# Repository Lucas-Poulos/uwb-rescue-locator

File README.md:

# UWB Rescue Locator

Repo: https://github.com/Lucas-Poulos/uwb-rescue-locator

A two-board UWB positioning system for a rescue/safety use case: a
**wristband** worn by a person, and a fixed **bay station** that locates it
in 3D from four anchor points and reports it over Bluetooth LE to a nearby
laptop (with an optional LTE-M uplink from the station).

Positioning is a **hybrid of two-way ranging and TDoA**, not symmetric
multilateration. A center anchor ranges to the tag for distance; three outer
anchors timestamp the same tag transmission and give direction from the
arrival-time differences. The four anchors are **not interchangeable** --
see [`docs/positioning.md`](docs/positioning.md), which is the document to
read first if you're working on anchors, clocking, coax, or connectors.

## Getting started (new contributor setup)

### 1. Install KiCad

The team standard is **KiCad 10.0.5** (see Toolchain below for why).

- **macOS**: `brew install --cask kicad` (Homebrew). If KiCad is already
  installed some other way, add `--force` to overwrite it.
- **Windows/Linux**: download the installer for your platform from
  https://www.kicad.org/download/.

You do **not** need to set any environment variables or configure library
paths yourself -- both boards' `fp-lib-table`/`sym-lib-table` use
`${KIPRJMOD}`-relative paths into this repo's own `shared/` and `libs/`
folders, so cloning the repo anywhere and opening a project just works.

The very first time you launch the KiCad GUI on a given machine, it may
offer to set up its own default global libraries (Device, Connector, etc.)
-- accept the defaults. This is a one-time, per-machine, KiCad-level setup
step, unrelated to this repo.

### 2. Get repo access and clone it

Ask whoever's administering the repo to add you as a collaborator (repo
link at the top of this file), then:

```
git clone git@github.com:Lucas-Poulos/uwb-rescue-locator.git
cd uwb-rescue-locator
```

(Use the HTTPS clone URL instead if you haven't set up an SSH key with
GitHub.)

### 3. Open a board

KiCad doesn't support one project spanning multiple PCBs, so open whichever
board you're working on directly -- there's no single top-level project
file for the whole repo:

```
open wristband/wristband.kicad_pro       # macOS; or just double-click the file
open bay-station/bay-station.kicad_pro
```

### 4. Sanity-check your setup

From a terminal, **outside** this repo (see the `kicad-cli` gotcha further
down for why):

```
cd /tmp
kicad-cli sch erc /path/to/uwb-rescue-locator/wristband/wristband.kicad_sch
```

If this reports a handful of known/expected items (see each board's sheet
table below) rather than a wall of "library not included in configuration"
errors, your KiCad install is set up correctly. If you do see that wall of
errors, see the per-major-version global library table note in Toolchain.

Before pushing anything, also read `CONTRIBUTING.md` -- branch off `main`,
don't edit a sheet someone else is actively working on, and PRs need review
(branch protection is on).

## Status (last updated 2026-11-18)

**Schematic capture is well along on the bay station and early on the
wristband.** On branch `redesign/nrf9151-host` every bay-station sheet has
been wired against one net contract (`docs/net-contract.md`). Neither board
is fab-ready: the bay station still has placeholder footprints on the TCXO,
SMA launch, MAX17048 and DNP eSIM (below). If you're an agent or a new teammate picking this
up cold, read this whole section before touching anything -- it's written to
be a complete handoff.

> ### Architecture change 2026-11-17: nRF9151 host
>
> The bay station's host moved from the Fanstel BT840 (nRF52840) to the
> **Nordic nRF9151** SiP -- LTE-M/NB-IoT modem, built-in GNSS and an
> application core. The nRF91 has no Bluetooth, so the **BT840 stays as a
> UART BLE bridge** to the laptop, and the **MAX-M10S GNSS is gone** (its
> sheet is now `orientation.kicad_sch`). Reasons and the full set of
> consequent calls are in `docs/decisions.md` ("nRF9151 host redesign").
>
> Unchanged, and still the core of the design: four discrete **DW3210**s on
> the one PCB sharing one 38.4 MHz TCXO through a 1:4 buffer, antennas remote
> on coax, A0 doing two-way ranging and A1-A3 TDoA against it
> (`docs/positioning.md`). **Target: 10-30 cm at ~10 m, Channel 5.** No FCC/CE
> work -- university prototype. The critical path is still **array
> calibration**, plus the multi-instance DW3000 driver.

### What exists, per board

The wristband has 7 hierarchical sheets, the bay station 10. Reference designators are
project-wide unique per board (checked 2026-11-17 on the bay station, no
collisions) -- see each `libs/components.csv` for the full part-by-part BOM.

**Wristband** (`wristband/`):
| Sheet | Status | Contents |
|---|---|---|
| Power BMS | **Wired** (global labels, no drawn wires), ERC clean (0 errors) | JST-PH battery -> AO3401A reverse-polarity FET -> TVS -> DW01A+FS8205A protection -> MCP73831 charger (USB-C in) |
| Radio MCU | **Wired**, ERC clean | DWM3001C (U4) + decoupling; SWD, RESET_N, SWO, VBAT_SENSE, SOS button, LED_SYS (P0.14), FW_MARKER (P0.22). One module: DW3110 UWB + nRF52833 MCU + accelerometer + both antennas |
| Mechanical | No wiring needed | 4x M2 mounting holes |
| Regulation | **Wired**, ERC clean | TPS7A0233PDBVR LDO (U5, 3.3V) -- battery hits 4.2V, DWM3001C tops out at 3.6V |
| Programming/Debug | **Wired**, ERC clean | ARM Cortex Debug SWD header (J3), targeting the nRF52833 inside U4 |
| Indicators | **Wired**, ERC clean | System LED D4 + R13 on nRF52833 P0.14; the charge LED (D2/R10, MCP73831 STAT) lives on Power BMS |
| Test Points | **Wired**, ERC clean | TP1-TP5: +3V3, VBAT, 2x GND, FW_MARKER (P0.22) |

**Bay Station** (`bay-station/`) -- per-sheet detail in each
`bay-station/*_notes.md`; sheet-by-sheet summary in `bay-station/README.md`:
| Sheet | Status | Contents |
|---|---|---|
| Power BMS | **Wired** | Barrel jack + USB-C -> MCP73871 power-path charger -> MAX17048 fuel gauge; backup cell with AO3401A + TVS. THERM window sized for cold-charge cutoff |
| Regulation | **Wired** | U8 TPS62A02 -> `+3V3`; **U40 TPS63802 buck-boost -> `+VBAT_LTE`** (nRF9151 VDD, 3.59 V); `+3V3` sequenced >= 6 ms after it; PPK2 break links on both rails |
| Connectivity | **Wired** | **nRF9151 (U20)** host with Nordic's HDG decoupling, LTE + GNSS (BGA524N6 LNA) on u.FL, nano-SIM (+ DNP eSIM); **BT840 (U3)** as UART BLE bridge |
| UWB Array | **Wired** | 4x DW3210 (U4=A0 center, U5-U7=A1-A3 outer), Qorvo Fig 32 decoupling, per-anchor 0R rework links, pi-match pads, SMA J20-J23 (proposed CONSMA020.042-G) |
| Clock Distribution | **Wired** | Proposed Rakon RPT1490LN TCXO -> TI LMK1C1104 1:4 buffer -> 2200 pF -> each XTI |
| Orientation (was GNSS / Orientation) | **Wired** | IIS2MDC magnetometer (U10, 0x1E) + IIS2DLPC accelerometer (U11, 0x19) |
| Indicators | **Wired** | D4-D6 charger status, D7 `LED_SYS`, D400 `LED_LTE`, D401 `LED_LINK`, resistors computed per rail |
| Programming/Debug | **Wired** | J3 nRF9151 SWD, J32 BT840 SWD, DNP Tag-Connect pads, J33 debug UART, SW2/SW11 resets, SW12 user button |
| Test Points | **Wired** | 64 pads covering every net-contract net (+ local pads on each sheet); index in `docs/verification-plan.md` |
| Mechanical | Placement only | 4x M3 mounting holes, 3 fiducials |

Whole-project ERC after the merge (2026-11-17, `kicad-cli` 10.0.5,
`--severity-all`): **7 warnings, 0 errors**, down from 596, with 432
components loaded (so not the silent `extends` failure). All 7 are
library-copy warnings, none connectivity: six `lib_symbol_mismatch` on
flattened stock symbols (BT1, Q1, J2, TH1, J3, J32) and, since the U8 lib_id
was renamed to `TPS62A02PDDC` on 2026-11-18, U8 (same count: the former
`lib_symbol_issues` became a seventh `lib_symbol_mismatch`; see
`docs/decisions.md`). The 97 `unconnected-*` nets
in the netlist are deliberate no-connect flags (spare BT840 GPIOs, nRF9151
reserved/MAGPIO pins, unused header pins). Per-sheet before/after counts are
in `bay-station/handoff/`.

### Confirmed chips/ICs (all sourced against real datasheets, not guessed)

| Part number | Role | Board(s) | Qty |
|---|---|---|---|
| Qorvo **DWM3001C** | UWB transceiver + nRF52833 MCU + LIS2DH12 accelerometer + both antennas, one module. Replaced NINA-B111 + DWM3000 + the antenna sheet | Wristband | 1 |
| Qorvo **DW3210** | Discrete UWB transceiver IC, QFN-40 5x5mm. One per anchor (U4=A0 center, U5-U7=A1-A3 outer). Chosen over the DWM3000 module because the module exposes no clock pin, and a shared reference is what makes the TDoA array work -- see `docs/positioning.md` | Bay Station | 4 |
| Qorvo **DWM3000** | UWB transceiver module. **No longer used on either board** -- the wristband moved to the DWM3001C and the bay station to discrete DW3210. Symbol and footprint are retained in `shared/` for reference only | -- | 0 |
| Microchip **MCP73831** | LiPo linear battery charger | Wristband | 1 |
| Fortune Semiconductor **DW01A** | Battery protection IC | Wristband | 1 |
| Fortune Semiconductor **FS8205** (commonly sold as "FS8205A" -- see `wristband/libs/README.md`) | Protection dual MOSFET, DW01A's partner IC | Wristband | 1 |
| AOS **AO3401A** | Reverse-battery-polarity protection P-MOSFET ("ideal diode") | Wristband + Bay Station | 2 |
| onsemi **ESD5B5.0ST1G** | TVS diode, battery/power-input protection | Wristband (1) + Bay Station (2) | 3 |
| Nordic **nRF9151** (nRF9151-LACA-R7) | Host SiP: LTE-M/NB-IoT modem + GNSS + Cortex-M33. Replaced the BT840 as host 2026-11-17. Footprint from Nordic's DK files (2026-11-18) | Bay Station | 1 |
| Fanstel **BT840** (Nordic nRF52840) | UART BLE bridge to the laptop (host until 2026-11-17; replaced ESP32-S3-WROOM-1 before that) | Bay Station | 1 |
| Microchip **MCP73871** | Charge management + power-path IC | Bay Station | 1 |
| Maxim/Analog Devices **MAX17048** | Battery fuel gauge (SOC monitor) | Bay Station | 1 |
| TI **TPS7A0233PDBVR** | LDO regulator (3.3V) -- battery rail can hit 4.2V, which exceeds the DWM3001C's 3.6V operating max without this. Replaced the MCP1700 on 2026-09-23 | Wristband | 1 |
| TI **TPS62A02PDDCR** | Buck regulator, `+VSYS` -> `+3V3` | Bay Station | 1 |
| TI **TPS63802DLAR** | Buck-boost, `+VSYS` -> `+VBAT_LTE` (nRF9151 VDD). Footprint from TI's land-pattern page (2026-11-18) | Bay Station | 1 |
| ST **IIS2MDC** / **IIS2DLPC** | Magnetometer (heading) / accelerometer (tilt, knock). Industrial grade with ST's 10-year longevity commitment; replaced the terminated LIS3MDL and the obsolete LIS2DH on 2026-11-18 | Bay Station | 1 + 1 |
| Infineon **BGA524N6** + TI **TPS7A0228** | GNSS LNA and its COEX0-switched 2.8 V LDO, as on the nRF9151 DK | Bay Station | 1 + 1 |
| TI **TPD3F303** | SIM ESD/EMI filter | Bay Station | 1 |
| Rakon **RPT1490LN** / TI **LMK1C1104** | 38.4 MHz CMOS TCXO / 1:4 clock buffer -- **PROPOSED**; the TCXO looks quote-only | Bay Station | 1 + 1 |

Footprint caveats: MAX17048 is flagged `_PLACEHOLDER` in its footprint file
-- pin/electrical data is fully verified, but one land-pattern dimension
needs re-checking against the real datasheet figure before fab (see
`bay-station/libs/README.md`). The same caveat applies to the DWM3000
footprint retained in `shared/`, though nothing uses it now. On the bay
station, the nRF9151 (U20), BT840 (U3) and TPS63802 (U40) footprints were
replaced on 2026-11-18 with vendor-sourced geometry (`docs/decisions.md`,
Resolved); the Rakon TCXO, the SMA edge launch (needs EM simulation) and the
DNP eSIM are still placeholders.

`U3` on both boards (BT840 and DWM3001C) and bay-station FB1-FB4 were given
footprints on 2026-11-18 (BT840 from Fanstel's library, DWM3001C from Qorvo's;
FB1-FB4 use stock 0201 pads, Murata land table not yet read).

Standard passive size for this whole project: **0603** for R/C/L (0-ohm
0603 link/jumper resistors are documented as a standard available option in
each `components.csv`, not yet placed on any sheet -- no specific
strap/bridge need identified yet).

Full reasoning/history for every choice above, plus the still-open
decisions (anchor placement, uplink backend, etc.), is in
`docs/decisions.md`.

### Known gotchas for whoever (human or agent) works on this next

- **kicad-cli silently fails on `extends`-based symbols.** Any cached
  schematic symbol using KiCad's `extends` mechanism (e.g. the default
  `AO3401A extends TP0610T`) makes `kicad-cli` fail to load the *entire
  file* and silently report it as empty (0 components, 0 ERC violations)
  rather than erroring loudly. Both boards work around this by embedding a
  flattened, non-`extends` copy of AO3401A. If a future sheet adds another
  `extends`-based part and ERC suspiciously shows 0 violations, check this
  first.
- **Always run `kicad-cli` from a scratch directory, never from inside a
  git repo.** It writes `.rpt` report files to the current working
  directory as a side effect; running it from inside a repo pollutes that
  repo's working tree with stray files.
- **KiCad's global library table is per-major-version and doesn't
  auto-populate from `kicad-cli` alone** -- see the Toolchain section below.
- **Don't leave a KiCad GUI window open on a project while also editing its
  files by hand/via script.** This happened once already: a background GUI
  session silently resaved `bay-station/power_bms.kicad_sch` in KiCad 10
  format while a concurrent edit was adding new sheets to the root file. No
  data was lost (verified via a reference-designator diff before
  committing), but it could have silently clobbered the newer edits if the
  stale window had been saved again afterward. Close/reload any open KiCad
  windows before doing further programmatic edits, and vice versa.
- The sibling project at `~/kicad-projects/wristband-alarm` (a *different*,
  unrelated wristband-alarm concept, also u-blox NINA-based) has its own
  long-standing uncommitted working-tree state -- don't touch it, don't
  assume its README reflects its actual working tree.

### Branches and workflow (as of 2026-11-18)

**There is no PR workflow.** Commit straight to the trunk branch and push;
no review gate (`CONTRIBUTING.md`, root `CLAUDE.md` rule 5). The trunk is
**`redesign/nrf9151-host`** -- the nRF9151-host bay station, the DW3210 array
and everything in this README -- until it replaces `main`. `main` still holds
the pre-redesign state (BT840 host, MAX-M10S) and is not where work happens;
branch protection on it has to be relaxed before anything can be pushed there.

What is where, so nobody resurrects the wrong thing:

- **Already merged into `main`** (before the redesign, all contained in the
  trunk): the Design Specifications section, the bay station power/regulation/
  programming-debug wiring pass, the no-external-wristband-IMU decision, PR #9
  (I2C pull-ups R37-R39) and PR #8 (per-anchor DW3210 decoupling, C40-C74 +
  FB1-FB4 + R33-R36, from Qorvo's reference design).
- **Superseded, do not merge: PR #7 / `feat/bay-station-wifi`** (ESP32-C5
  Wi-Fi co-processor). The nRF9151 redesign replaced the host it was written
  against; the station's second uplink is LTE-M, and there are no GPIOs left
  for a Wi-Fi co-processor (`docs/decisions.md`, Resolved, "Process"). The
  GitHub PR is still open and can be closed from the web UI.
- **Historical branches, not ancestors of the trunk:** `dwm3001c-migration`
  (the wristband work; it landed on `main` through the rebased branch in
  PR #5, so the original is redundant), `backup/dwm3001c-pre-rebase` (a
  safety copy of the same), and `nina-b400-migration` (an earlier u-blox
  NINA-B400 / DWM3000-module schematic pass, last touched 2026-09-20; its
  contents were not reviewed for this rewrite). Reference only -- run
  `git branch -a --no-merged redesign/nrf9151-host` before assuming a branch
  holds work that matters.

Merging history worth knowing: PR #8 and PR #9 conflicted textually with the
power-wiring pass because `connectivity.kicad_sch` and `uwb_array.kicad_sch`
had been reserialized to KiCad 10 format in between, and were hand-ported onto
the reserialized files (`b7ab51f`, `4ef1099`; balanced parens, no duplicate
references, ERC showing exactly the expected violation delta). That was done
carefully and checked, not the norm -- `CONTRIBUTING.md`'s warning about
silent corruption from hand-resolving `.kicad_sch` conflicts still stands.

### Not done yet (in rough next-up order)

1. **Re-verify every Nordic fact against the PDFs** -- so far they were
   read only from Nordic's HTML pages (`docs/decisions.md`, Open). The
   nRF9151 footprint itself now comes from Nordic's DK files; compare it with
   the PS land-pattern figure when the PDF is in hand.
2. **Footprints**: BT840, DWM3001C, U40 and nRF9151 are done (2026-11-18);
   still open are FB1-FB4 (read Murata's BLM03PG land table), the TCXO,
   the SMA launch and the DNP eSIM.
3. **Close the redesign's open risks** in `docs/decisions.md`. Analysed
   2026-11-18 and reduced to concrete actions: the DW3210 has **no exposed
   pad** (footprint since replaced), the 8 MHz SPI cap is a reply-delay
   measurement not a throughput problem, XTI amplitude is at the DW3000 limit
   and needs a bench check, and there is a ranked list of ways to free GPIOs
   (one is free since the sensor re-pick: P0.24). The terminated LIS3MDL and
   obsolete LIS2DH were replaced by the IIS2MDC / IIS2DLPC on 2026-11-18. Still open: TCXO availability (quote), GNSS LNA
   pre-filter.
4. **Array calibration procedure and fixture** -- the project's critical
   path; drafted in `docs/verification-plan.md`.
5. **Firmware**: the NCS skeletons exist but have never been built; the
   multi-instance DW3000 driver is the gating task (`firmware/README.md`).
6. Wire the wristband's placement-only sheets (independent of everything
   above).
7. PCB layout. The bay station's `.kicad_pcb` has its **4-layer
   controlled-impedance stackup** set from DW3000 Section 7.3.2 Figure 35
   (1.048mm finished); since 2026-11-18 it also has the board outline and all 428 footprints placed (unrouted;
   `docs/layout-notes.md`).
   **The wristband's `.kicad_pcb` is not an empty stub** -- it already carries
   36 footprints, a routed board outline, and real DRC findings from the
   DWM3001C migration (PR #5); U3 (the DWM3001C) now has a footprint in the library (2026-11-18) but the PCB
   still embeds the old placeholder until it is updated from the schematic.

Done since the last update, for the record: the anchor rework onto four
discrete DW3210s, the decoupling audit (`docs/passives-reference.md`), the
two-USB-C item (deleted with the ESP32), the antenna-matching task (deleted
with the wristband's antenna sheet), the L1 and SW2 footprints, the
cold-charge THERM sizing, and the bay station's GPIO allocation.

## System overview

```
                         A1 ← antenna on coax
                            \
   ┌─────────────┐           \      ┌────────────────────────────┐
   │  Wristband   │  UWB       ○────│  Bay Station (ONE PCB)     │
   │  (worn tag)  │ ═════════▶ A0   │  4x DW3210, one TCXO       │
   └─────────────┘  one TX    / \   │  nRF9151 host (LTE-M+GNSS) │
                             /   \  │  BT840 BLE bridge (UART)   │
                           A2     A3└──────┬──────────────┬──────┘
                      antennas on ~1-2 m   │ Bluetooth LE │ LTE-M
                      coax, rigid frame    ▼              ▼ (optional)
                                         Laptop        network

   A0     two-way ranging  -> range to tag
   A1-A3  TDoA vs. A0      -> direction to tag

   All four transceivers share one clock on the board.
   Only the antennas are remote.
```

- **Wristband**: one Qorvo DWM3001C (UWB + nRF52833 MCU + antennas) +
  a compact BMS (MCP73831 charger + DW01A/FS8205 protection + AO3401A
  reverse-polarity protection). Design compromises favor small size and
  just enough battery life to get core functionality working. In the
  positioning scheme its job is simply to transmit -- one transmission
  yields all four measurements, deliberately, because the tag is the
  power-constrained side.
- **Bay station**: four UWB receivers in two roles (one center, three outer)
  on a single PCB sharing one TCXO, an nRF9151 host (LTE-M + GNSS) with a
  Fanstel BT840 bridging to a laptop over BLE, and a BMS designed for long
  runtime rather than small size (MCP73871 power-path charger + MAX17048 fuel
  gauge), since the bay station isn't worn. The four antennas sit on ~1-2 m coax runs to a rigid frame --
  that's what buys the baseline the bearing measurement needs.

There's no physical connector between the wristband and the bay station --
their only interface is the UWB radio link. The bay station's own antennas
are wired to it over SMA coax (CH5 at 6489.6 MHz is above U.FL's 6 GHz
rating). See `docs/system-overview.md` and `docs/positioning.md`.

## Design specifications

Quick-reference only -- full reasoning, error budgets, and datasheet
citations live in `docs/positioning.md` (RF/clock/mechanical) and
`docs/decisions.md` (every component/architecture call). Anything not listed
here as resolved is still an open decision; check there before assuming a
number is final.

**Performance target**
| | |
|---|---|
| Accuracy | 10-30 cm |
| Range | ~10 m |
| Baseline (A0-to-outer-antenna spacing) | ~1 m as built; frame size is the real limit, not cable loss |

**RF**
| | |
|---|---|
| UWB channel | Channel 5, 6489.6 MHz |
| UWB IC, bay station | 4x Qorvo DW3210 (QFN40, non-PDoA) -- U4=A0 center, U5-U7=A1-A3 outer |
| UWB IC, wristband | Qorvo DW3110 (WLCSP), inside the DWM3001C module |
| UWB connectors | SMA -- CH5 is above U.FL/W.FL/MMCX/MCX's 6 GHz rating and SMB's 4 GHz rating |
| Link budget | 86 dB available (CH5, 850 kbps, 1024-symbol preamble); ~17 dB margin at 10 m |
| Antennas (bay station) | Not yet selected -- candidates covering CH5: Taoglas UWC.01 / ILA.68 / UWCCP.01 |

**Clock (bay station array)**
| | |
|---|---|
| Reference | One 38.4 MHz TCXO -> 1:4 low-skew fan-out buffer -> all 4 DW3210 XTI pins |
| Coupling | 2200 pF AC-coupled into each XTI; 1 pF from each XTO to ground |
| TCXO spec | 0.8 V-VDD2 Vpp, -132 dBc/Hz @ 1 kHz, -145 dBc/Hz @ 10 kHz, 40-60% duty (DW3000 Datasheet Table 10) |
| TCXO + buffer part numbers | Rakon RPT1490LN + TI LMK1C1104 -- PROPOSED, TCXO availability open |

**Positioning architecture**
Hybrid two-way-ranging + TDoA, not symmetric multilateration -- see
`docs/positioning.md` for the full derivation.
| | |
|---|---|
| Center anchor (A0) | Two-way ranging with the wristband -> range |
| Outer anchors (A1-A3) | TDoA vs. A0 on the same tag transmission -> direction |
| System | 4 equations, 3 unknowns -- overdetermined by 1; use the residual as a quality metric |
| Mechanical | Rigid frame fixes geometry (no install-time survey); A0 offset 20-30 cm out of the A1-A3 plane to avoid a mirror ambiguity |
| Array calibration | Required, not optional (generic +/-6 cm spec is 3x too loose at this baseline); procedure/fixture still open |

**Power**
| | Wristband | Bay station |
|---|---|---|
| Regulator | TI TPS7A0233PDBVR LDO, 3.3V | TI TPS62A02PDDCR buck -> `+3V3`, 2A; TI TPS63802 buck-boost -> `+VBAT_LTE` 3.59 V, 2A |
| Load vs. rating | ~43 mA (4.6x headroom) | `+3V3` ~356 mA peak (~446 mA worst case); `+VBAT_LTE` 505 mA LTE TX subframe -- >= 4x headroom on both (`docs/decisions.md`) |
| Standby | ~2.7 uA | n/a -- BMS optimized for runtime, not size |

**Connectivity**
| | |
|---|---|
| Wristband <-> bay station | UWB only -- one tag transmission per exchange, no other radio link |
| Bay station -> laptop | Bluetooth LE via the BT840 bridge (NUS, framed relay, raw timestamps) -- primary path, no WiFi |
| Bay station -> network | LTE-M from the nRF9151, optional (station must work with no SIM); service still open |
| Georeferencing | nRF9151 GNSS (time-shared with LTE) + ST IIS2MDC magnetometer + ST IIS2DLPC accelerometer (bay station only; position + heading both required) |

**Cost** (one prototype pair, hobbyist qty-1 pricing -- see `docs/bom-cost.md`)
| | |
|---|---|
| Wristband | ~$67 |
| Bay station | ~$263 + unpriced rows (nRF9151, TCXO, ...) |
| Total | ~$330 + unpriced rows |

**Regulatory**
No FCC/CE certification -- university prototype, not sold or deployed as a
product. Revisit as a first-class schedule item if that ever changes.

**Toolchain**
| | |
|---|---|
| KiCad | 10.0.5 (files on disk still in 8.0 format) |
| MCUs | All Nordic -- nRF52833 (wristband, inside DWM3001C) / nRF9151 host + nRF52840 BLE bridge (bay station, the latter inside the Fanstel BT840) |
| Firmware SDK | nRF Connect SDK v3.4.x (LTS), all images; nRF9151 modem FW 2.0.4 |

## Repo layout

```
shared/                      # symbols/footprints/3D models used on BOTH boards (e.g. the UWB IC)
  symbols/                   # shared .kicad_sym library
  footprints/                # shared .pretty footprint library
  3dmodels/                  # shared .step/.wrl models
wristband/                   # KiCad project: the wearable tag
  wristband.kicad_pro/sch/pcb
  libs/                      # wristband-only symbols/footprints
bay-station/                 # KiCad project: the fixed 4-anchor station
  bay-station.kicad_pro/sch/pcb
  libs/                      # bay-station-only symbols/footprints
docs/
  positioning.md             # the ToF + TDoA scheme, error budget, clock architecture
  system-overview.md         # block diagram + RF/data interface between the boards
  decisions.md               # open + resolved component/architecture decisions log
  passives-reference.md      # every chip's reference-design passives, compiled per-chip
  bom-cost.md                # build cost estimate for one prototype pair
  net-contract.md            # bay-station cross-sheet net names
  verification-plan.md       # bay-station bring-up/test plan + test-point index
firmware/                    # NCS firmware (nRF9151 / BT840 / nRF52833) -- skeletons, never built
CLAUDE.md                    # working rules for Claude Code / other coding agents
CONTRIBUTING.md              # git workflow, sheet conventions, pre-push checks
```

Each board is its own KiCad project (KiCad doesn't support one project
spanning multiple PCBs), but both live in this one repo so shared parts,
docs, and history stay in one place. Each project's `fp-lib-table` /
`sym-lib-table` reference the `shared/` libraries via `${KIPRJMOD}` relative
paths, so this works regardless of where the repo is cloned -- no per-machine
setup needed.

## Toolchain

Files are currently in **KiCad 8.0** format, originally authored/verified
against KiCad 8.0.6. As of 2026-08-14 this machine has been upgraded to
**KiCad 10.0.5** (the actual current stable -- confirmed as the team's
standard, superseding an earlier, since-corrected plan to target KiCad 9.x).
All existing files were re-checked with
`kicad-cli` under 10.0.5 (`sch erc`/`pcb drc`) and open/parse cleanly with no
new issues -- opening a file in the newer GUI and re-saving is still a
one-way, zero-cost upgrade whenever the team wants to bump the file format
itself; nothing has been re-saved yet, so the files on disk are still 8.0
format.

Note for anyone else upgrading KiCad's major version: `kicad-cli` alone
won't auto-populate the new version's global symbol/footprint library table
(`~/Library/Preferences/kicad/<version>/sym-lib-table` /`fp-lib-table`) --
that normally happens the first time you launch the actual KiCad GUI and it
offers to migrate/create settings. If you only ever use `kicad-cli`
headlessly without opening the GUI first, you may see a wall of spurious
"library not included in configuration" ERC errors -- just launch KiCad.app
once (or copy the two `*-lib-table` files from
`.../KiCad.app/Contents/SharedSupport/template/`) to fix it.

## Using Claude Code (or another coding agent) on this project

**The working rules for agents live in [`CLAUDE.md`](CLAUDE.md)** -- Claude
Code picks that up automatically. This section is the human-readable version
of why those rules exist.

KiCad's file formats (`.kicad_sch`, `.kicad_pcb`, `.kicad_pro`, `.kicad_sym`,
`.kicad_mod`) are plain text (S-expression or JSON) -- an agent can read and
edit them directly like any other source file, no special MCP server or
plugin required. Everything in this repo so far was built that way. A few
things make it work reliably, several of them learned the hard way in this
repo's own history:

- **`kicad-cli` is the fast headless sanity check.** After any edit, run
  `kicad-cli sch erc <board>.kicad_sch` and `kicad-cli pcb drc
  <board>.kicad_pcb` before trusting a change.
  - **macOS**: a Homebrew install symlinks it onto `PATH` automatically
    (`/opt/homebrew/bin/kicad-cli`); otherwise it's inside the app bundle at
    `/Applications/KiCad/KiCad.app/Contents/MacOS/kicad-cli`.
  - **Windows**: the official installer puts it on `PATH` automatically; if
    not, it's at `C:\Program Files\KiCad\10.0\bin\kicad-cli.exe`.
  - **Linux**: on `PATH` automatically via most package managers (apt,
    dnf, etc.) or the official AppImage/flatpak.
- **Always run `kicad-cli` from a scratch/temp directory, never from
  inside this repo.** It writes `.rpt` report files to the current working
  directory as a side effect -- running it from inside a git repo (this
  one or any other) pollutes the working tree with stray files. This has
  actually happened once already, to an unrelated sibling project, from a
  leftover `cd`.
- **`kicad-cli` silently fails on `extends`-based symbols.** A cached
  schematic symbol using KiCad's `extends` mechanism (e.g. the default
  library's `AO3401A extends TP0610T`) makes `kicad-cli` fail to load the
  *entire file* and report it as empty (0 components, 0 ERC violations)
  instead of erroring loudly -- a suspiciously clean ERC run is a red flag,
  not necessarily good news. This repo works around it everywhere by
  embedding flattened, non-`extends` copies of any such symbols (see
  `docs/decisions.md` and the various `*_notes.md` files for examples).
- **Use an existing sheet/symbol/footprint as the format template before
  writing a new one.** Every file in this repo was built by reading a
  known-good file first -- either one already in this repo, or one of
  KiCad's own bundled default libraries -- and matching its exact
  structure, rather than freehand-authoring the s-expression format from
  memory. This repo uses literal tab characters for indentation, not
  spaces; match that.
- **Don't run scripted file edits at the same time as a live KiCad GUI
  session has the same project open.** A background GUI window doesn't
  know about changes made outside it, and saving from a stale window can
  silently overwrite newer edits -- this already caused one near-miss on
  the bay station board (see "Known gotchas" above). Close/reload any open
  KiCad windows before scripted edits, and vice versa. A lock file at
  `<board>/~<board>.kicad_pro.lck` means a GUI session currently has that
  project open.
- **Verify real datasheet facts (pinouts, voltage ratings, current draw)
  by actually fetching and reading the datasheet PDF**, not from memory or
  a search-result summary -- several real bugs/gaps in this repo were only
  caught this way (e.g. the wristband's missing voltage regulator, a
  part-number that doesn't actually exist, a mislabeled SOT-23-6 part).
- **pcbnew's Python bindings** are available for programmatic
  footprint/board work (generating a blank `.kicad_pcb`, loading a
  footprint to sanity-check its pad count, etc.) via KiCad's own bundled
  Python interpreter -- **not** your system Python, which won't have the
  `pcbnew` module installed:
  - **macOS**: `/Applications/KiCad/KiCad.app/Contents/Frameworks/Python.framework/Versions/Current/bin/python3`
  - **Windows**: typically `C:\Program Files\KiCad\10.0\bin\python.exe`
  - **Linux**: usually just your system `python3` if KiCad was installed via
    a package manager that wires up the `pcbnew` module for it; otherwise
    check your distro's KiCad packaging docs.

## Will this work on both Mac and Windows?

Yes, and this has actually been checked, not just assumed:

- No absolute Mac-specific paths are baked into any `.kicad_pro`/`.kicad_sch`/
  `.kicad_pcb`/library file (`git grep`-checked) -- all cross-file/library
  references use `${KIPRJMOD}`-relative paths, which KiCad resolves
  identically on every OS.
- No filenames in this repo use characters or reserved names that are
  illegal on Windows (`: * ? " < > |`, or `CON`/`PRN`/`AUX`/`NUL`/`COM1-9`/
  `LPT1-9`), and no path exceeds even a fraction of Windows' historical
  260-character path limit (longest path in this repo is 80 characters).
- All tracked files use consistent LF line endings, and `.gitattributes`
  normalizes this going forward so a Windows contributor's git config
  (which sometimes auto-converts line endings on checkout) can't silently
  turn KiCad files into CRLF and create noisy diffs or merge pain.

What differs by platform is purely the install step and a couple of tool
paths (both covered above/in Getting Started) -- KiCad itself, the file
formats, and this repo's structure are fully cross-platform.

## Contributing

See `CONTRIBUTING.md` for the git workflow (branching, hierarchical-sheet
conventions to avoid merge conflicts, pre-push checks).

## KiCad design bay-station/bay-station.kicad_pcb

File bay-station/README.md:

# Bay Station

The fixed reference station. Open `bay-station.kicad_pro` in KiCad.

## Scope

- **UWB anchors**: four DW3210 transceivers, all on this PCB sharing one
  38.4 MHz TCXO, in two distinct roles -- one **center** anchor (A0) that
  does two-way ranging with the wristband, and three **outer** anchors that
  measure TDoA against it. Range plus direction gives a 3D fix. The four
  **antennas** are remote, on ~1-2 m SMA coax runs to a rigid frame. Read
  `../docs/positioning.md` before touching anything in the anchor, clock,
  coax, or connector path.
- **Host MCU + links**: Nordic **nRF9151** SiP (U20, resolved 2026-11-17)
  -- drives the four DW3210s, reads the sensors, and has an LTE-M modem and
  GNSS built in. It has no Bluetooth, so the Fanstel **BT840** (U3,
  nRF52840) stays as a **UART BLE bridge** to a nearby laptop, which remains
  the primary link; LTE-M is optional (the station must work with no SIM).
  See `../docs/decisions.md`, "nRF9151 host redesign".
- **Georeferencing**: nRF9151 GNSS for position, IIS2MDC + IIS2DLPC for heading
  and tilt (`orientation.kicad_sch`).
- **BMS**: optimized for longevity rather than size, since this board isn't
  worn (contrast with the wristband's compromise-heavy BMS).

Target performance: **10-30 cm at ~10 m, on Channel 5 (6489.6 MHz)**.

> **Every sheet is wired against `../docs/net-contract.md`; the footprints are
> placed and outlined but nothing is routed (`../docs/layout-notes.md`), and
> the board is not fab-ready.** The nRF9151, BT840 and TPS63802
> footprints now come from vendor files (2026-11-18; `libs/README.md`). Still
> blocking fab: the TCXO, SMA-launch, MAX17048 and DNP eSIM footprints are
> placeholders, FB1-FB4's land pattern is unverified, and all Nordic facts
> were read from Nordic's HTML pages, not the PDFs. Full list:
> `../docs/decisions.md`, Open.
>
> **Array calibration is a deliverable, not a bring-up nicety** -- the design
> does not meet its accuracy target without it. See `../docs/decisions.md`.

## Status

Ten hierarchical sheets, all registered in `bay-station.kicad_pro`'s
`sheets` list and wired into `bay-station.kicad_sch` as sheet symbols. Each
sheet's detail, citations and bring-up tests live in its `*_notes.md`; this
table is the summary. Pins are assigned in one place:
`connectivity_notes.md` section 2.

| Sheet | Status | Contents | Notes |
|---|---|---|---|
| `power_bms` | **Wired** | Barrel jack + USB-C in (`+5V_IN`) -> MCP73871 power-path -> `+VSYS`; MAX17048 gauge on `I2C_SCL/SDA`; backup cell with AO3401A + TVS; THERM window sized (+1..+5 degC cold cutoff) | `power_bms_notes.md` |
| `regulation` | **Wired** | U8 TPS62A02 -> `+3V3`; U40 TPS63802 buck-boost -> `+VBAT_LTE` 3.59 V (nRF9151 VDD); `+3V3` sequenced >= 6 ms after it; UVLO 2.91 V; R300/R302 PPK2 break links | `regulation_notes.md` |
| `connectivity` | **Wired** | U20 nRF9151 + HDG decoupling; LTE (J10) and GNSS (J11, BGA524N6 LNA) on u.FL; nano-SIM + DNP eSIM; U3 BT840 bridge; I2C pull-ups R37/R38 3.3k, R39 2.2k | `connectivity_notes.md` |
| `uwb_array` | **Wired** | 4x DW3210 (U4 = A0 center, U5-U7 = A1-A3 outer), Fig 32 decoupling, per-anchor 0R links, SPI-mode-0 straps, pi-match pads, SMA J20-J23, XTO caps C28-C31, DNP A0 fallback crystal | `uwb_array_notes.md` |
| `clock_dist` | **Wired** | Proposed RPT1490LN TCXO -> LMK1C1104 -> 22R -> 2200 pF -> `UWB_CLK0..3`; no `TCXO_EN` | `clock_dist_notes.md` |
| `orientation` (was `gnss`) | **Wired** | IIS2MDC (U10, 0x1E) + IIS2DLPC (U11, 0x19) on `+3V3_SNS`; MAX-M10S removed | sheet notes; `components.csv` |
| `indicators` | **Wired** | D4/D5 (STAT1/STAT2, from `+VSYS`), D6 (PG, from `+5V_IN`), D7 `LED_SYS`, D400 `LED_LTE`, D401 `LED_LINK` | `../docs/decisions.md`, LED drive rails |
| `programming_debug` | **Wired** | J3 nRF9151 SWD, J32 BT840 SWD, DNP Tag-Connect J34/J35, J33 debug UART, SW2/SW11 resets, SW12 `BTN_USER` | `programming_debug_notes.md` |
| `testpoints` | **Wired** | 62 pads project-wide (cut from 127 on 2026-11-18: 42 on this sheet, the other 20 local to regulation 8, connectivity 5, power_bms 3, clock_dist 3, orientation 1): rails incl. far ends, shared SPI, per-anchor CSn/IRQ, interrupts, resets, 7 GND springs; clock pads TP5/TP6 behind DNP 0R. Labels and function groups: `../scripts/layout/testpoint_labels.json` | `../docs/verification-plan.md`, Test-point index and "Cut pads and why" |
| `mechanical` | Placement only | H1-H4 (M3, NPTH), FID1-FID3 | grounding the holes is Open |

**ERC.** Each sheet owner ran `kicad-cli` ERC on the whole project during
the 2026-11-17 redesign and recorded before/after counts in
`handoff/*.md` (596 before; 0-10 per redesigned sheet afterwards, the rest
cross-sheet items waiting on the other branches). A
whole-project count for the merged branch has not been recorded here yet --
re-run it before quoting a number. U8's lib_id was renamed to `TPS62A02PDDC`
on 2026-11-18, so its warning is now a `lib_symbol_mismatch`
(`../docs/decisions.md`).

### The PCB

`bay-station.kicad_pcb` now carries the **4-layer controlled-impedance
stackup** (F.Cu / prepreg 254um / In1.Cu / core 400um / In2.Cu / prepreg
254um / B.Cu, 35um copper throughout, 1.048mm finished), taken from DW3000
Datasheet v1.3 Section 7.3.2 Figure 35. Until 2026-09-23 the file was an
empty 2-layer default stub, which contradicted a decision the docs had
already recorded as settled. The rest of Section 7.3 -- 50 ohm RF1/RF2,
ground cutouts under each DW3210, group separation -- is written as a note
on the board's `Cmts.User` layer, where layout will actually see it.

The dielectric numbers (er 4.5, tan d 0.02) are KiCad's FR4 defaults, not
datasheet values. Controlled impedance means the fab's stackup wins.

**Placement only (2026-11-18).** All 428 footprints are placed on the top side inside a
128 x 68 mm rounded outline with 4 M3 holes and 3 fiducials, generated by
`../scripts/layout/place_bay_station.py`; there are no tracks, vias or filled zones. The
floorplan, rationale, metrics and the unverified assumptions (SMA edge launch, connector
mating faces, BT840 antenna side) are in `../docs/layout-notes.md`. The SMA footprints'
20 copper-to-edge DRC errors are expected until the launch is simulated.

Every part now has a footprint (U3, U20, U40 and FB1-FB4 were assigned
2026-11-18). Placeholders that must be replaced before fab: **U30** (Rakon
TCXO), **J20-J23** (SMA launch, needs EM simulation), **U23** (DNP eSIM),
the MAX17048 fuel gauge. FB1-FB4 use stock 0201 pads pending Murata's land table.
See `../docs/decisions.md`.

### Sheet detail

Moved into the per-sheet notes files listed in the Status table, which are
kept current with each change; the earlier prose summaries here had gone
stale (they still described the BT840 as host). Two pieces of history worth
keeping in view:

- `programming_debug` was rebuilt for Nordic on 2026-09-19, deleting the
  ESP32-S3 boot straps, EN RC, BOOT button and the data USB-C -- which is why
  the board has a single, power-only USB-C (`J2`).
- `uwb_array` kept R10-R17 (GPIO5/6 SPI-mode straps) and R25-R28 (IRQ
  pull-downs, Qorvo Figure 11) through the module-to-IC move, because both
  are DW3000-core requirements; the module-era C8-C19 were deleted.

### Next up

1. **Replace the nRF9151 footprint** with Nordic's real land pattern and
   re-verify the Nordic facts against the PDFs.
2. **Import the BT840 footprint**; resolve U40, FB1-FB4, TCXO and SMA
   footprints; design the SMA launch.
3. **Re-run whole-project ERC** on the merged branch and record it above.
4. ~~Draw the board outline~~ -- done 2026-11-18 (128 x 68 mm, `../docs/layout-notes.md`);
   routing, the 50 ohm launch design and the equal-length clock meanders are next.
5. Work through the Open items in `../docs/decisions.md` -- TCXO
   availability, GNSS pre-filter, cable loss, array
   calibration. (No FCC/CE work: university prototype, not certified.)

## Libraries

- `libs/` -- bay-station-only symbols/footprints
- `../shared/` -- parts used on both boards (registered via
  `fp-lib-table`/`sym-lib-table`)

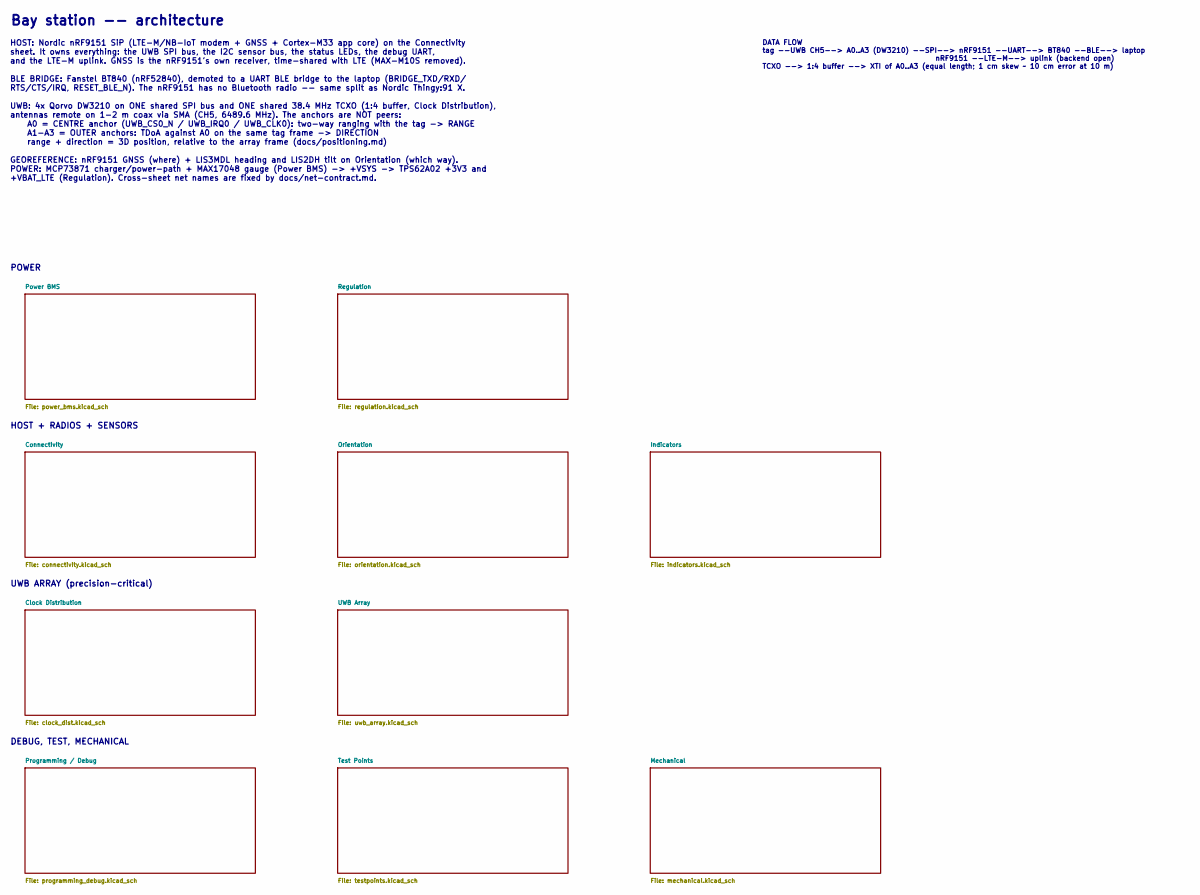
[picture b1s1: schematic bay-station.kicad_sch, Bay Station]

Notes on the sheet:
DATA FLOW tag --UWB CH5--> A0..A3 (DW3210) --SPI--> nRF9151 --UART--> BT840 --BLE--> laptop nRF9151 --LTE-M--> uplink (backend open) TCXO --> 1:4 buffer --> XTI of A0..A3 (equal length; 1 cm skew ~ 10 cm error at 10 m)
HOST: Nordic nRF9151 SiP (LTE-M/NB-IoT modem + GNSS + Cortex-M33 app core) on the Connectivity sheet. It owns everything: the UWB SPI bus, the I2C sensor bus, the status LEDs, the debug UART, and the LTE-M uplink. GNSS is the nRF9151's own receiver, time-shared with LTE (MAX-M10S removed). BLE BRID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
HOST + RADIOS + SENSORS
Bay station -- architecture
DEBUG, TEST, MECHANICAL
POWER
UWB ARRAY (precision-critical)

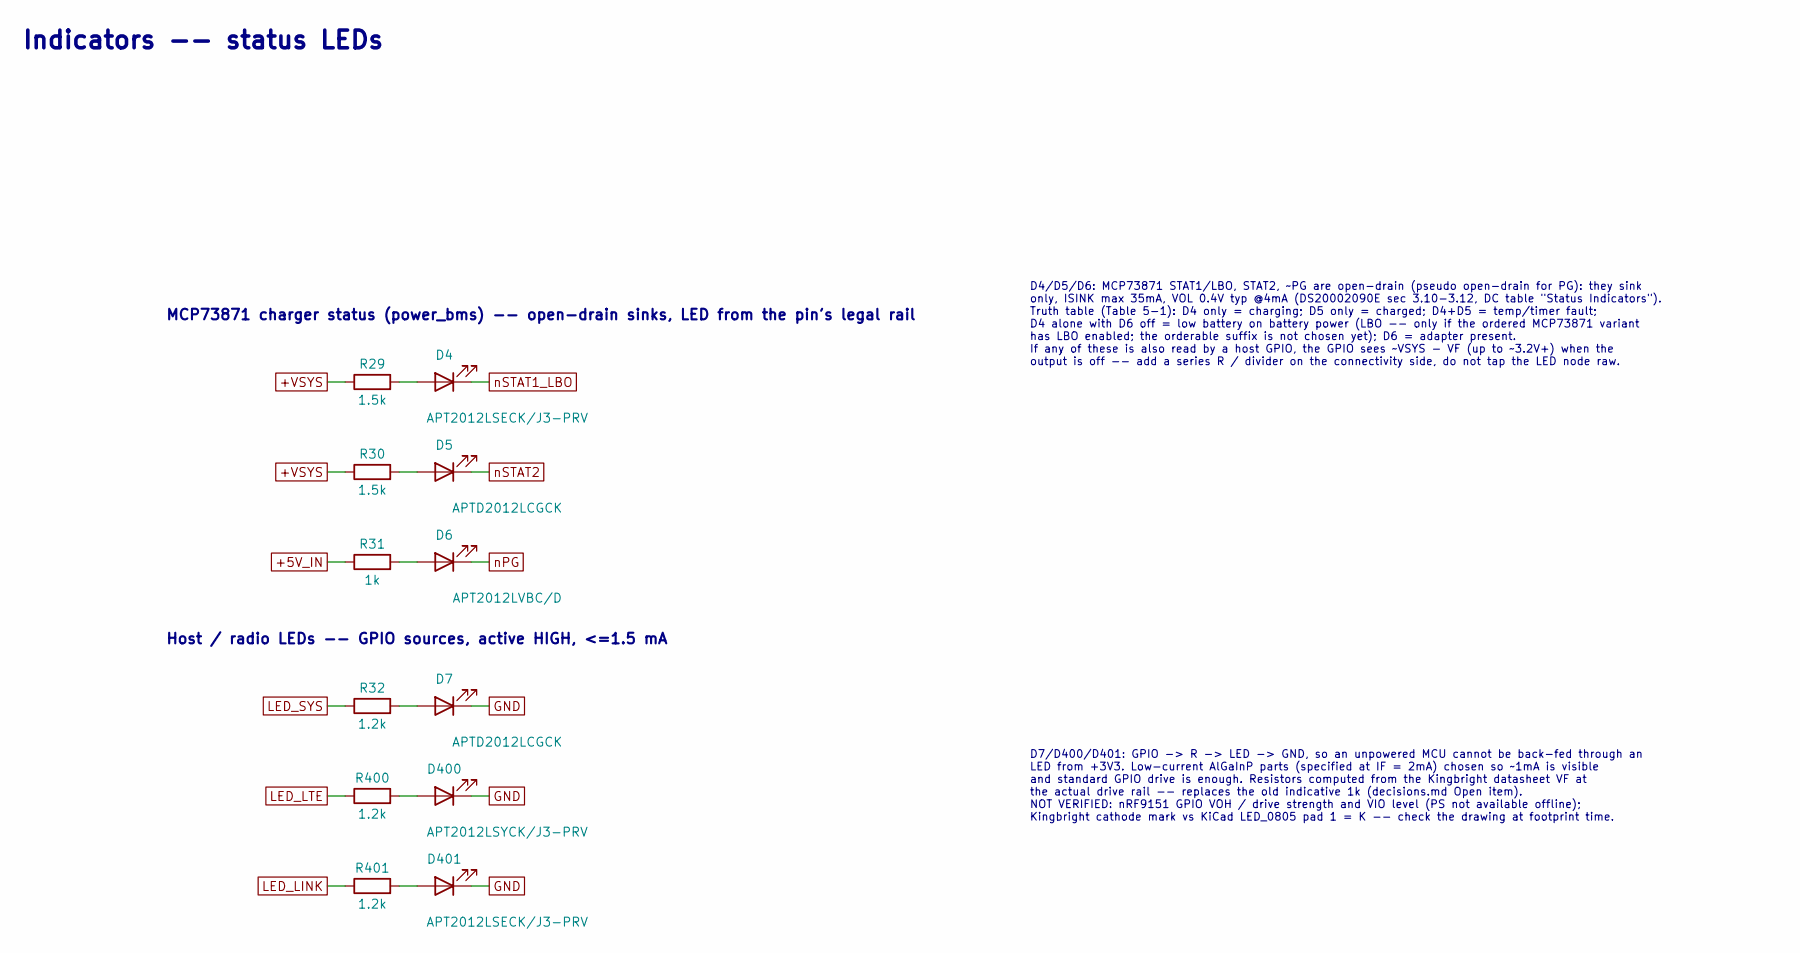
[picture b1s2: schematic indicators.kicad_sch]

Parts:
D4, D401: APT2012LSECK/J3-PRV; LED_0805_2012Metric
D5, D7: APTD2012LCGCK; LED_0805_2012Metric
D6: APT2012LVBC/D; LED_0805_2012Metric
D400: APT2012LSYCK/J3-PRV; LED_0805_2012Metric
R29, R30: 1.5k; R_0603_1608Metric
R31: 1k; R_0603_1608Metric
R32, R400, R401: 1.2k; R_0603_1608Metric

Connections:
+5V_IN: R31.1; also elsewhere on the board
+VSYS: R29.1, R30.1; also elsewhere on the board
GND: D7.1 (K), D400.1 (K), D401.1 (K); also elsewhere on the board
LED_LINK: R401.1; also elsewhere on the board
LED_LTE: R400.1; also elsewhere on the board
LED_SYS: R32.1; also elsewhere on the board
unnamed: D4.2 (A), R29.2
unnamed: D5.2 (A), R30.2
unnamed: D6.2 (A), R31.2
unnamed: D7.2 (A), R32.2
unnamed: D400.2 (A), R400.2
unnamed: D401.2 (A), R401.2
nPG: D6.1 (K); also elsewhere on the board
nSTAT1_LBO: D4.1 (K); also elsewhere on the board
nSTAT2: D5.1 (K); also elsewhere on the board

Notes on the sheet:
Indicators -- status LEDs
D4/D5/D6: MCP73871 STAT1/LBO, STAT2, ~PG are open-drain (pseudo open-drain for PG): they sink only, ISINK max 35mA, VOL 0.4V typ @4mA (DS20002090E sec 3.10-3.12, DC table "Status Indicators"). Truth table (Table 5-1): D4 only = charging; D5 only = charged; D4+D5 = temp/timer fault; D4 alone with D6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
D7/D400/D401: GPIO -> R -> LED -> GND, so an unpowered MCU cannot be back-fed through an LED from +3V3. Low-current AlGaInP parts (specified at IF = 2mA) chosen so ~1mA is visible and standard GPIO drive is enough. Resistors computed from the Kingbright datasheet VF at the actual drive rail -- repl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
MCP73871 charger status (power_bms) -- open-drain sinks, LED from the pin's legal rail
Host / radio LEDs -- GPIO sources, active HIGH, <=1.5 mA

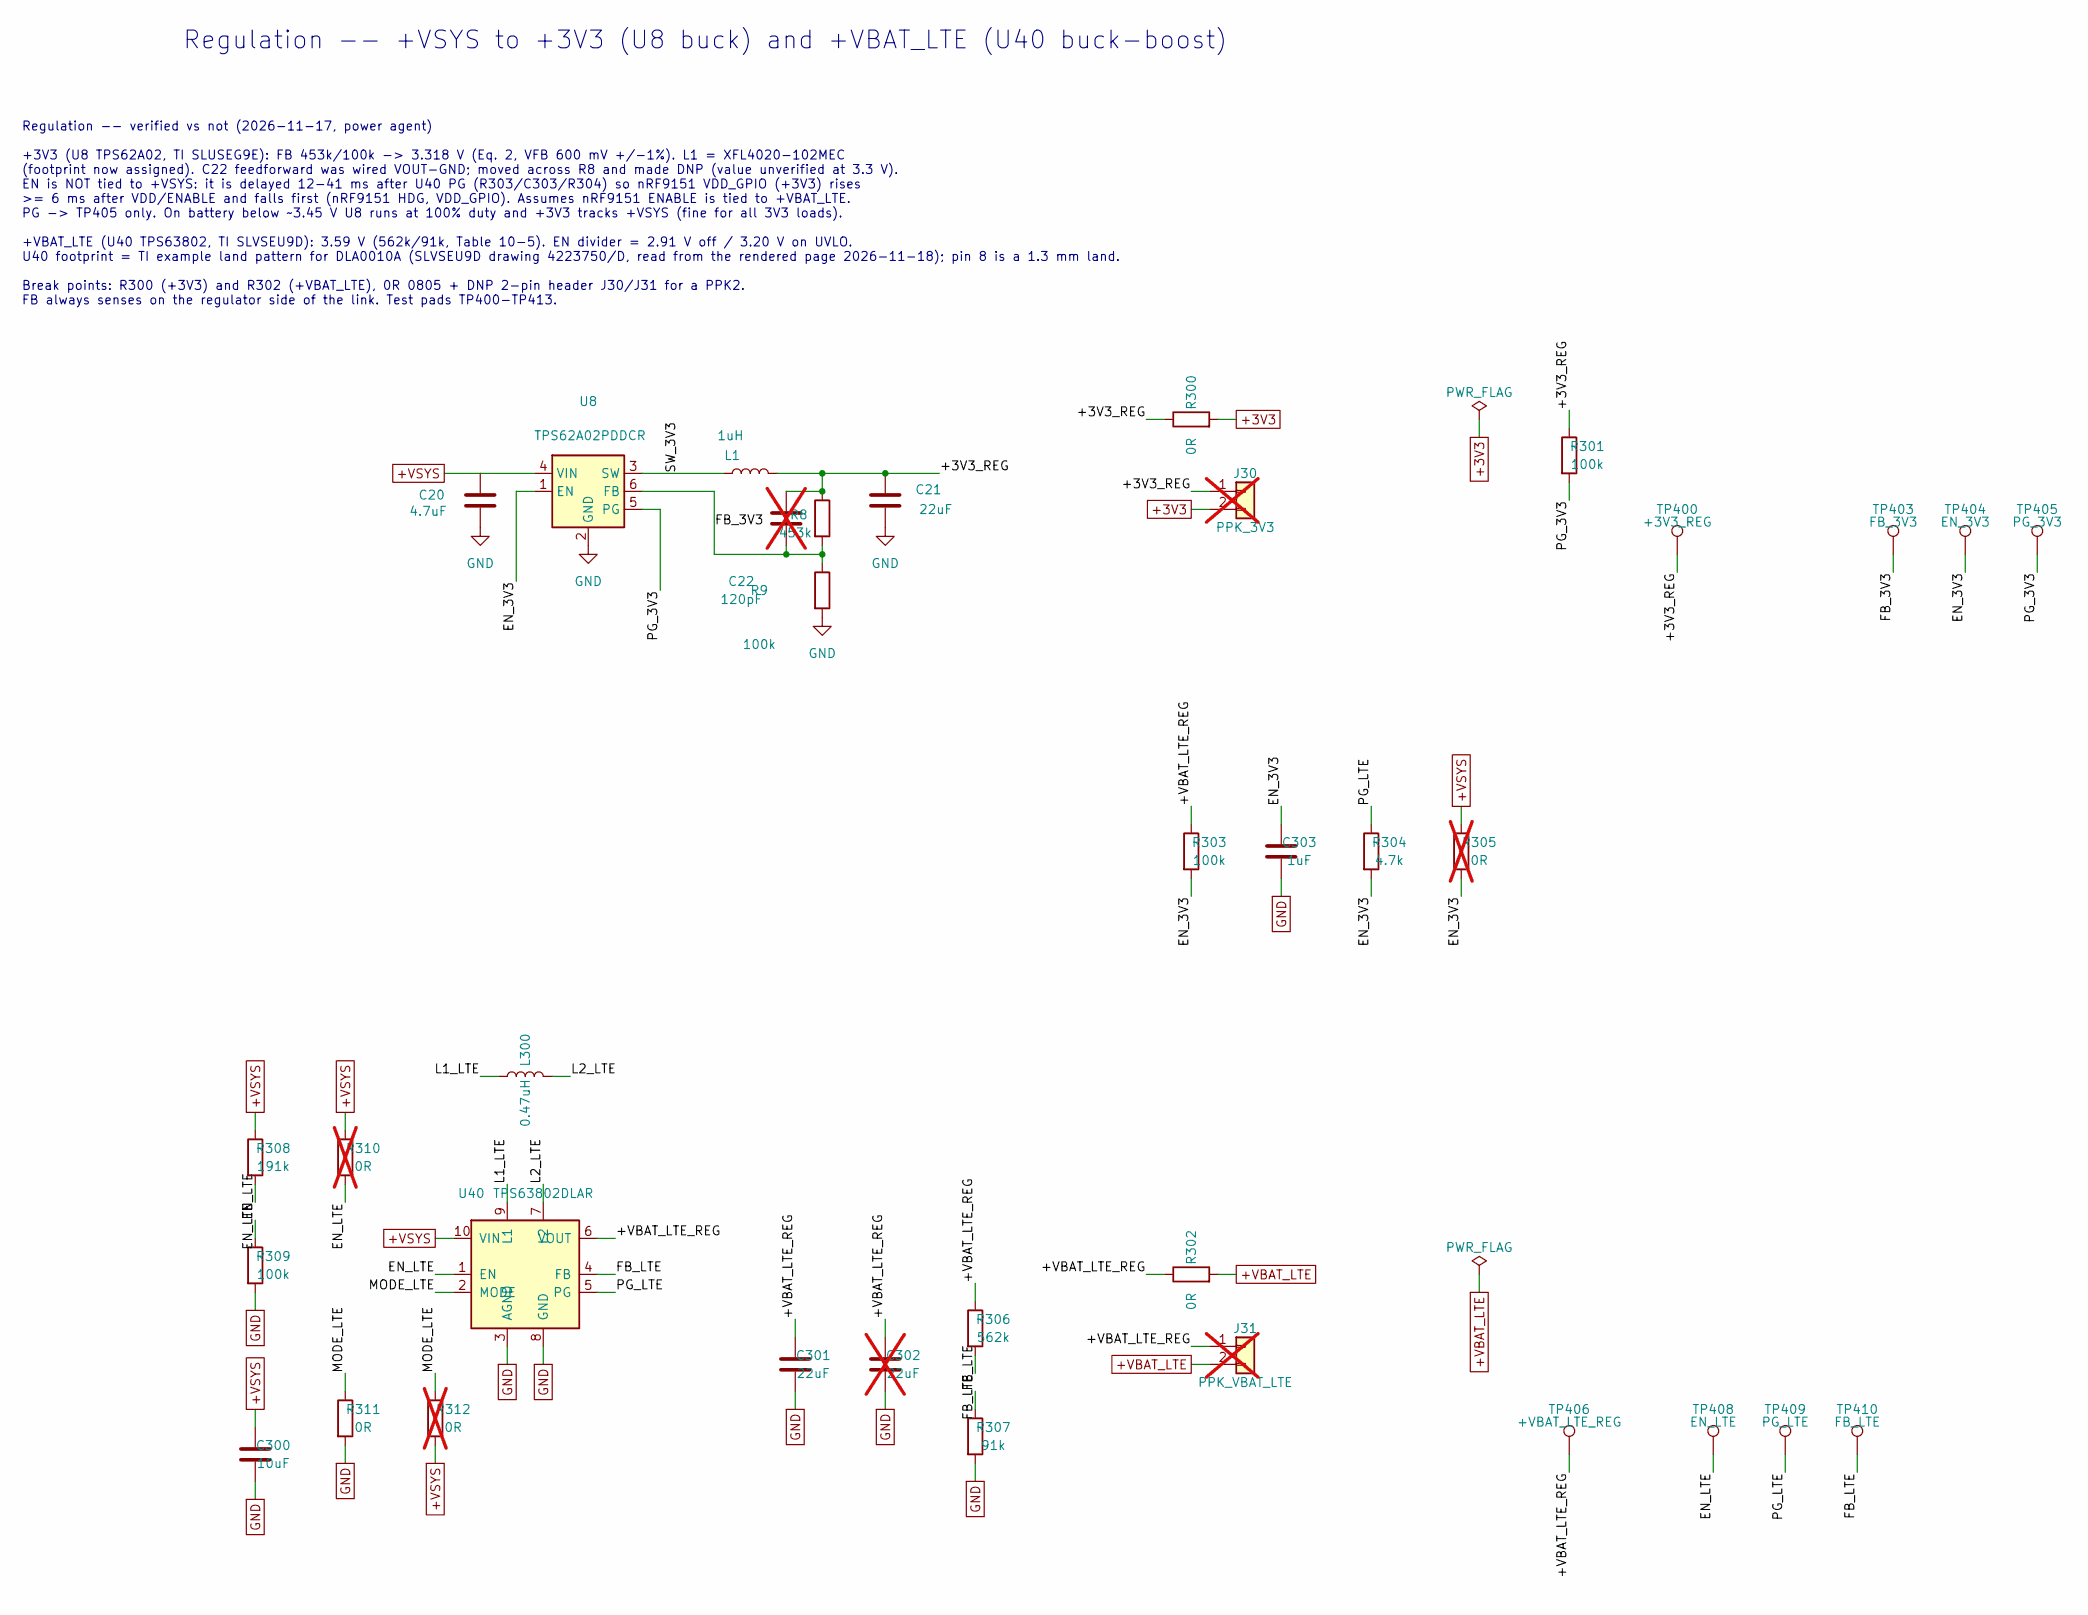
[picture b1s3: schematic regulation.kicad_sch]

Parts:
C20: 4.7uF; C_0805_2012Metric
C21, C301: 22uF; C_0805_2012Metric
C22: 120pF; C_0603_1608Metric; not fitted
C300: 10uF; C_0805_2012Metric
C302: 22uF; C_0805_2012Metric; not fitted
C303: 1uF; C_0603_1608Metric
J30: PPK_3V3; PinHeader_1x02_P2.54mm_Vertical; not fitted
J31: PPK_VBAT_LTE; PinHeader_1x02_P2.54mm_Vertical; not fitted
L1: 1uH; L_Coilcraft_XxL4020
L300: 0.47uH; L_Coilcraft_XxL4020; MPN XFL4020-471MEC
R8: 453k; R_0603_1608Metric
R9, R301, R303, R309: 100k; R_0603_1608Metric
R300, R302: 0R; R_0805_2012Metric
R304: 4.7k; R_0603_1608Metric
R305, R310, R312: 0R; R_0603_1608Metric; not fitted
R306: 562k; R_0603_1608Metric
R307: 91k; R_0603_1608Metric
R308: 191k; R_0603_1608Metric
R311: 0R; R_0603_1608Metric
TP400: +3V3_REG; TestPoint_Pad_D1.0mm
TP403: FB_3V3; TestPoint_Pad_D1.0mm
TP404: EN_3V3; TestPoint_Pad_D1.0mm
TP405: PG_3V3; TestPoint_Pad_D1.0mm
TP406: +VBAT_LTE_REG; TestPoint_Pad_D1.0mm
TP408: EN_LTE; TestPoint_Pad_D1.0mm
TP409: PG_LTE; TestPoint_Pad_D1.0mm
TP410: FB_LTE; TestPoint_Pad_D1.0mm
U8: TPS62A02PDDCR; SOT-23-6
U40: TPS63802DLAR; TI_DLA0010A_VSON-HR-10_2x3mm_P0.5mm; MPN TPS63802DLAR

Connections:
+3V3: J30.2, R300.2; also elsewhere on the board
+VBAT_LTE: J31.2, R302.2; also elsewhere on the board
+VSYS: C20.1, C300.1, R305.1, R308.1, R310.1, R312.2, U8.4 (VIN), U40.10 (VIN); also elsewhere on the board
/Regulation/+3V3_REG: C21.1, C22.1, J30.1, L1.2, R8.1, R300.1, R301.1, TP400.1 (1_1)
/Regulation/+VBAT_LTE_REG: C301.1, C302.1, J31.1, R302.1, R303.1, R306.1, TP406.1 (1_1), U40.6 (VOUT)
/Regulation/EN_3V3: C303.1, R303.2, R304.2, R305.2, TP404.1 (1_1), U8.1 (EN)
/Regulation/EN_LTE: R308.2, R309.1, R310.2, TP408.1 (1_1), U40.1 (EN)
/Regulation/FB_3V3: C22.2, R8.2, R9.1, TP403.1 (1_1), U8.6 (FB)
/Regulation/FB_LTE: R306.2, R307.1, TP410.1 (1_1), U40.4 (FB)
/Regulation/L1_LTE: L300.1, U40.9 (L1)
/Regulation/L2_LTE: L300.2, U40.7 (L2)
/Regulation/MODE_LTE: R311.1, R312.1, U40.2 (MODE)
/Regulation/PG_3V3: R301.2, TP405.1 (1_1), U8.5 (PG)
/Regulation/PG_LTE: R304.1, TP409.1 (1_1), U40.5 (PG)
/Regulation/SW_3V3: L1.1, U8.3 (SW)
GND: C20.2, C21.2, C300.2, C301.2, C302.2, C303.2, R9.2, R307.2, R309.2, R311.2, U8.2 (GND), U40.3 (AGND), U40.8 (GND); also elsewhere on the board

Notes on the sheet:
Regulation -- +VSYS to +3V3 (U8 buck) and +VBAT_LTE (U40 buck-boost)
Regulation -- verified vs not (2026-11-17, power agent) +3V3 (U8 TPS62A02, TI SLUSEG9E): FB 453k/100k -> 3.318 V (Eq. 2, VFB 600 mV +/-1%). L1 = XFL4020-102MEC (footprint now assigned). C22 feedforward was wired VOUT-GND; moved across R8 and made DNP (value unverified at 3.3 V). EN is NOT tied to +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
